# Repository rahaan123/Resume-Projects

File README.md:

# Resume-Projects
Projects listed here are mentioned on resume.

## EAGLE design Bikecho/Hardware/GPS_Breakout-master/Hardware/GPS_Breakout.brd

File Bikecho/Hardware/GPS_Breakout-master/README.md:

GPS Breakout
========================================

[  
*GPS Breakout (BOB-11818)*](https://www.sparkfun.com/products/11818)

This is a universal breakout board for any GPS units that interface over 1.0mm JST type cable. This board currently is compatible with the [GP-635T](https://www.sparkfun.com/products/11571), [GP-735](https://www.sparkfun.com/products/13670) [EM406](https://www.sparkfun.com/products/465), and [EM506](https://www.sparkfun.com/products/12751) GPS receviers and the [1 foot](https://www.sparkfun.com/products/9123) and [1.75 inch](https://www.sparkfun.com/products/574) JST cables.

Repository Contents
-------------------
* **/Hardware** - All Eagle design files (.brd, .sch)
* **/Production Files** - Test bed files and production panel files

Documentation
-------------------

* **[Hookup Guide](https://learn.sparkfun.com/tutorials/gps-basics/all#reading-gps-data)** - Basic hookup guide using the GPS breakout board.

License Information
-------------------
The hardware is released under [Creative Commons Share-alike 3.0](http://creativecommons.org/licenses/by-sa/3.0/).

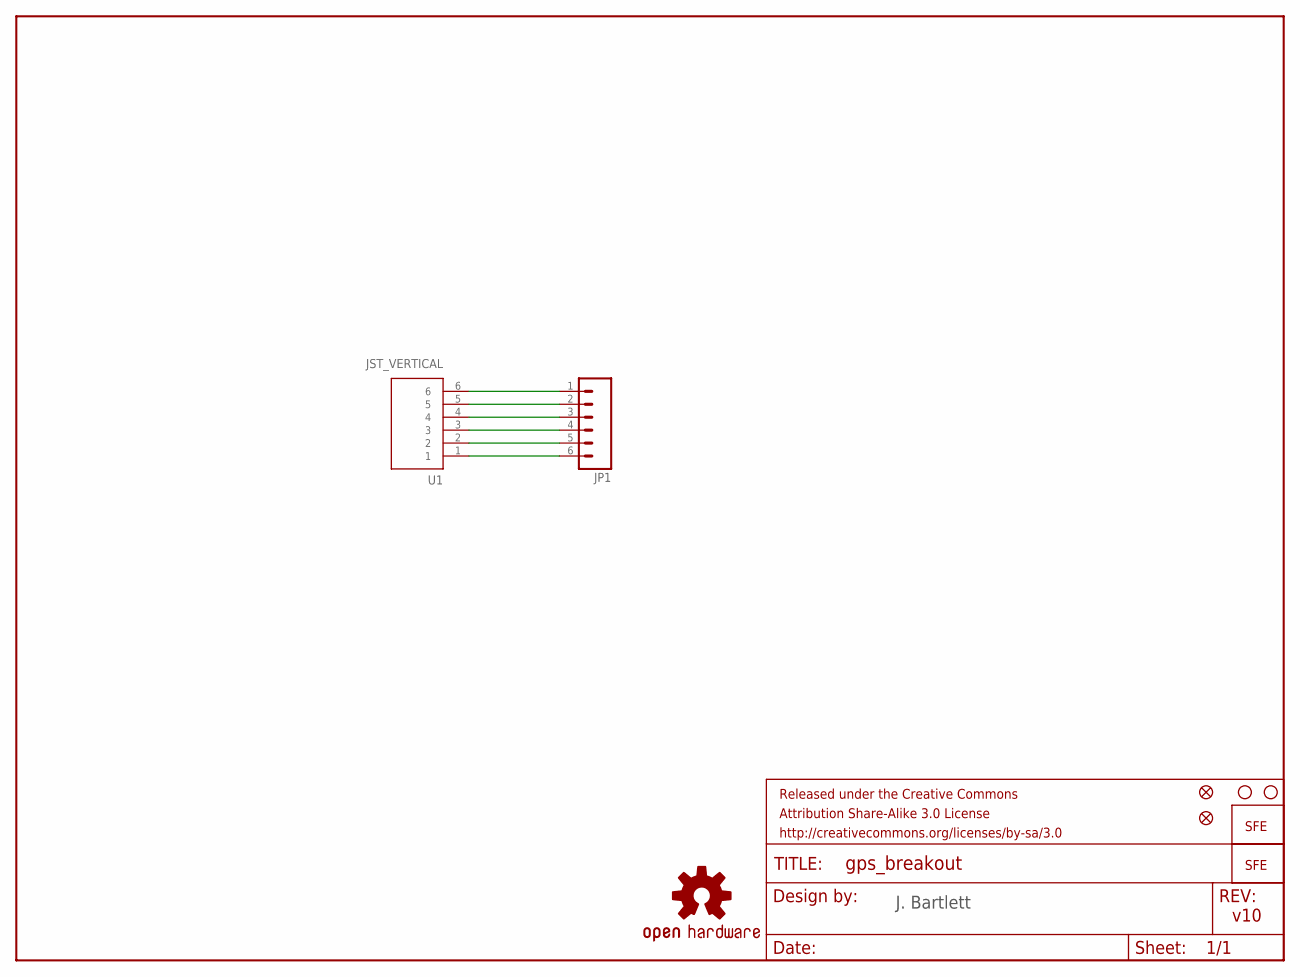
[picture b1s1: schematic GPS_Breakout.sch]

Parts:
FID1, FID2: FIDUCIALUFIDUCIAL; MICRO-FIDUCIAL
FRAME2: FRAME-LETTER; CREATIVE_COMMONS
JP1: M06SIP; 1X06
JP2, JP7: LOGO-SFESK; SFE-LOGO-FLAME
JP4, JP6: STAND-OFF
LOGO1: OSHW-LOGOS; OSHW-LOGO-S
U1: JST_VERTICAL; JST-6-SMD-VERT-1.0MM

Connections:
unnamed: JP1.1, U1.6
unnamed: JP1.2, U1.5
unnamed: JP1.3, U1.4
unnamed: JP1.4, U1.3
unnamed: JP1.5, U1.2
unnamed: JP1.6, U1.1

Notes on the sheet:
J. Bartlett
v10

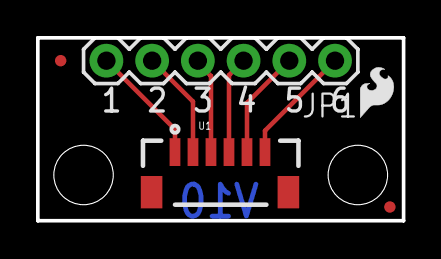
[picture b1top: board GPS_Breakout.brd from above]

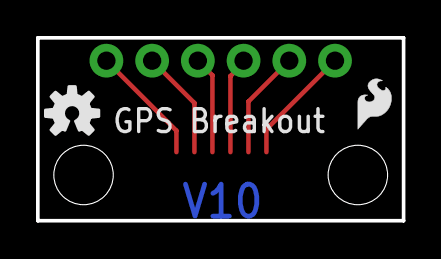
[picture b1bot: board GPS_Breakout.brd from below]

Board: 2 copper layers, 20.3 x 10.2 mm, 10 parts (2 on the bottom side), 6 nets.

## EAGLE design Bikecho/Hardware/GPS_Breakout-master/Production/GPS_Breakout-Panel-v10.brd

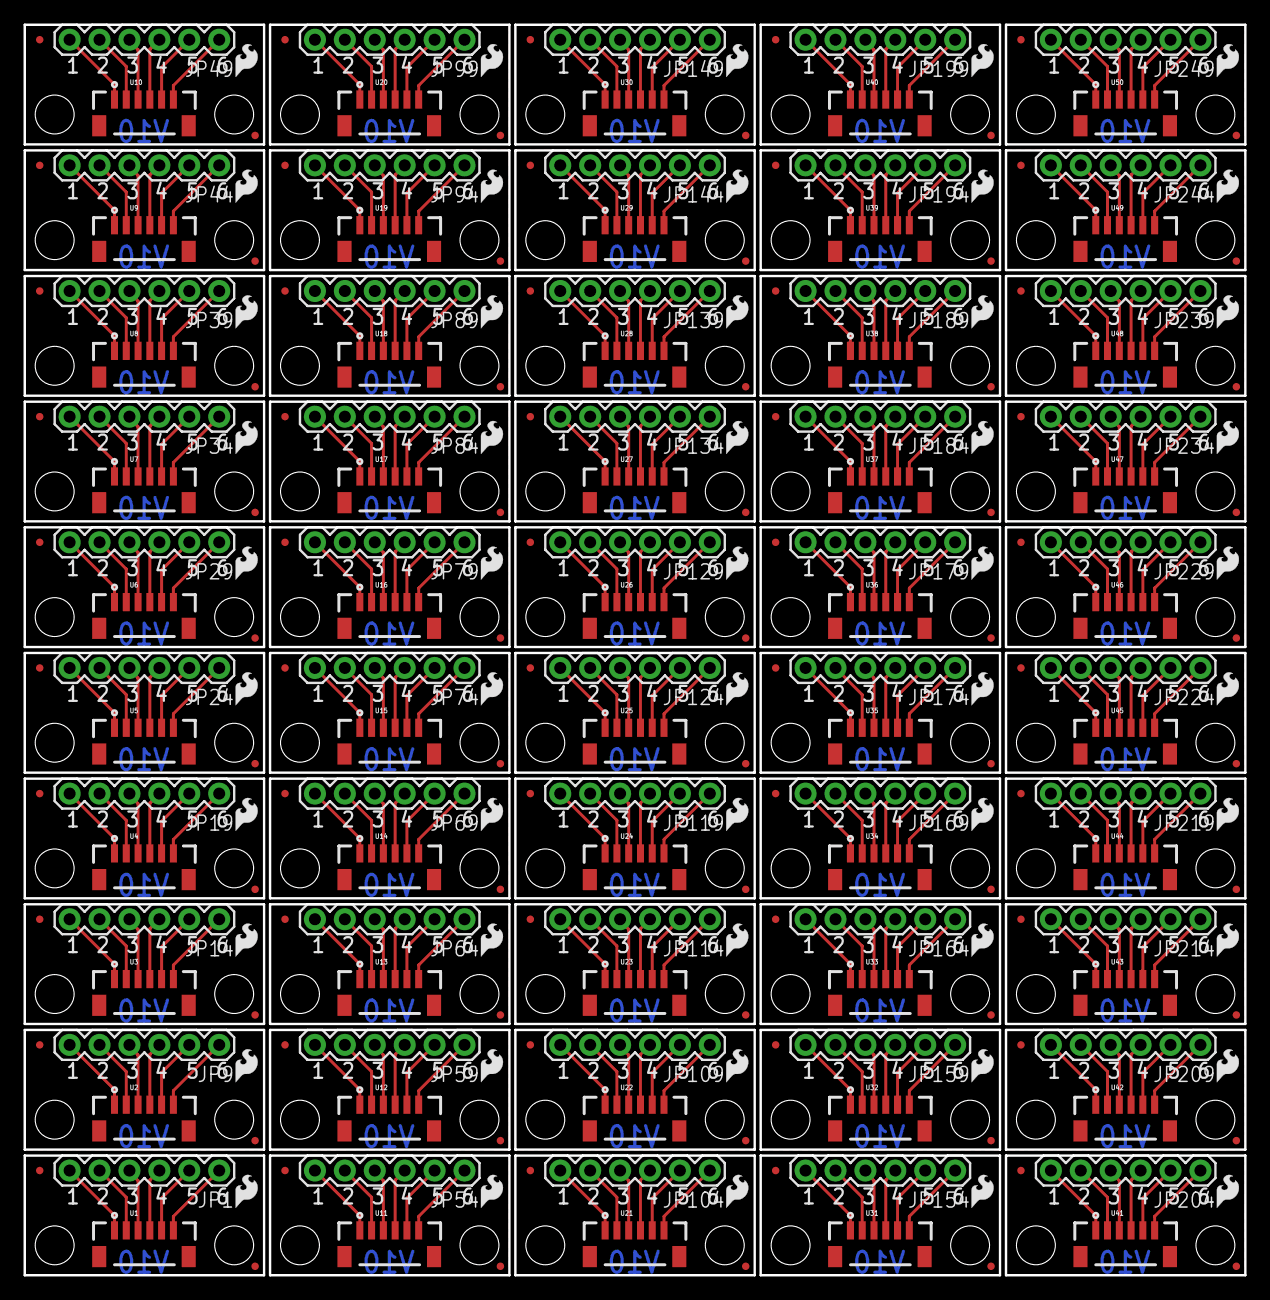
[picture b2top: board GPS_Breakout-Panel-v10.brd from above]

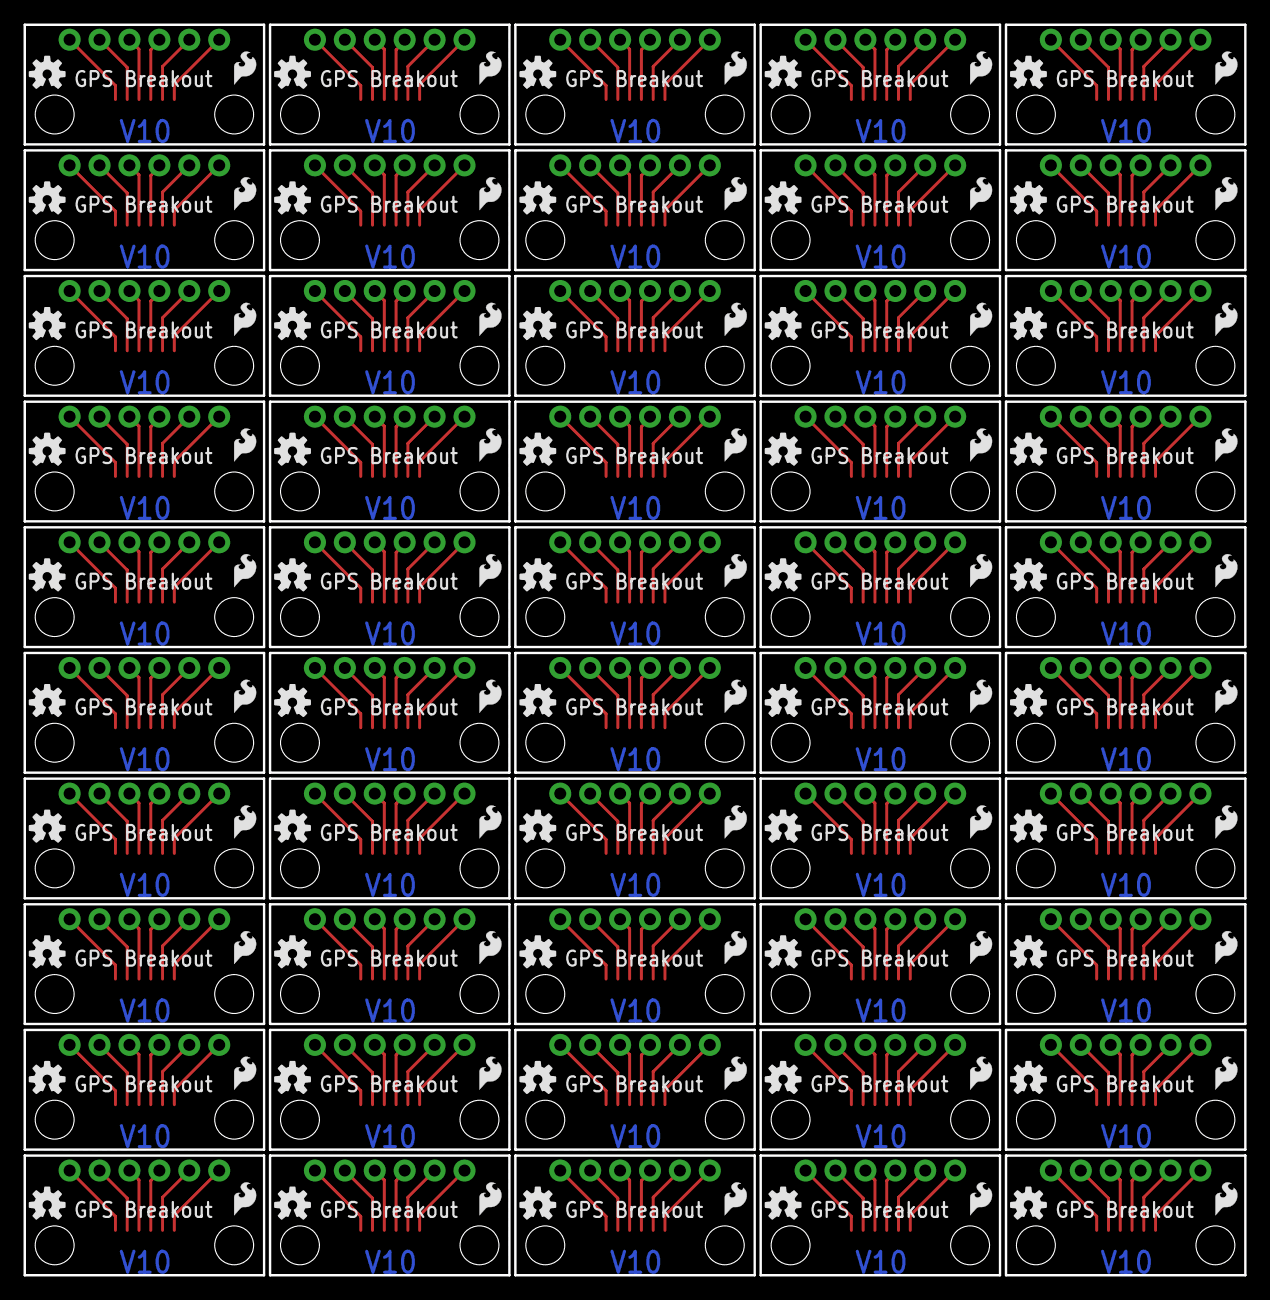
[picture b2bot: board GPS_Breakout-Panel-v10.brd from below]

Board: 2 copper layers, 103.6 x 106.2 mm, 450 parts (100 on the bottom side), 300 nets.

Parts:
FID1, FID2, FID3, FID4, FID5, FID6, FID7, FID8, FID9, FID10, FID11, FID12, FID13, FID14, FID15, FID16, FID17, FID18, FID19, FID20, FID21, FID22, FID23, FID24, FID25, FID26, FID27, FID28, FID29, FID30, FID31, FID32, FID33, FID34, FID35, FID36, FID37, FID38, FID39, FID40, FID41, FID42, FID43, FID44, FID45, FID46, FID47, FID48, FID49, FID50, FID51, FID52, FID53, FID54, FID55, FID56, FID57, FID58, FID59, FID60, FID61, FID62, FID63, FID64, FID65, FID66, FID67, FID68, FID69, FID70, FID71, FID72, FID73, FID74, FID75, FID76, FID77, FID78, FID79, FID80, FID81, FID82, FID83, FID84, FID85, FID86, FID87, FID88, FID89, FID90, FID91, FID92, FID93, FID94, FID95, FID96, FID97, FID98, FID99, FID100: FIDUCIALUFIDUCIAL; MICRO-FIDUCIAL
JP1, JP9, JP14, JP19, JP24, JP29, JP34, JP39, JP44, JP49, JP54, JP59, JP64, JP69, JP74, JP79, JP84, JP89, JP94, JP99, JP104, JP109, JP114, JP119, JP124, JP129, JP134, JP139, JP144, JP149, JP154, JP159, JP164, JP169, JP174, JP179, JP184, JP189, JP194, JP199, JP204, JP209, JP214, JP219, JP224, JP229, JP234, JP239, JP244, JP249: 1X06
JP2, JP7, JP8, JP10, JP13, JP15, JP18, JP20, JP23, JP25, JP28, JP30, JP33, JP35, JP38, JP40, JP43, JP45, JP48, JP50, JP53, JP55, JP58, JP60, JP63, JP65, JP68, JP70, JP73, JP75, JP78, JP80, JP83, JP85, JP88, JP90, JP93, JP95, JP98, JP100, JP103, JP105, JP108, JP110, JP113, JP115, JP118, JP120, JP123, JP125, JP128, JP130, JP133, JP135, JP138, JP140, JP143, JP145, JP148, JP150, JP153, JP155, JP158, JP160, JP163, JP165, JP168, JP170, JP173, JP175, JP178, JP180, JP183, JP185, JP188, JP190, JP193, JP195, JP198, JP200, JP203, JP205, JP208, JP210, JP213, JP215, JP218, JP220, JP223, JP225, JP228, JP230, JP233, JP235, JP238, JP240, JP243, JP245, JP248, JP250: LOGO-SFESK; SFE-LOGO-FLAME
JP3, JP4, JP5, JP6, JP11, JP12, JP16, JP17, JP21, JP22, JP26, JP27, JP31, JP32, JP36, JP37, JP41, JP42, JP46, JP47, JP51, JP52, JP56, JP57, JP61, JP62, JP66, JP67, JP71, JP72, JP76, JP77, JP81, JP82, JP86, JP87, JP91, JP92, JP96, JP97, JP101, JP102, JP106, JP107, JP111, JP112, JP116, JP117, JP121, JP122, JP126, JP127, JP131, JP132, JP136, JP137, JP141, JP142, JP146, JP147, JP151, JP152, JP156, JP157, JP161, JP162, JP166, JP167, JP171, JP172, JP176, JP177, JP181, JP182, JP186, JP187, JP191, JP192, JP196, JP197, JP201, JP202, JP206, JP207, JP211, JP212, JP216, JP217, JP221, JP222, JP226, JP227, JP231, JP232, JP236, JP237, JP241, JP242, JP246, JP247: STAND-OFF
LOGO1, LOGO2, LOGO3, LOGO4, LOGO5, LOGO6, LOGO7, LOGO8, LOGO9, LOGO10, LOGO11, LOGO12, LOGO13, LOGO14, LOGO15, LOGO16, LOGO17, LOGO18, LOGO19, LOGO20, LOGO21, LOGO22, LOGO23, LOGO24, LOGO25, LOGO26, LOGO27, LOGO28, LOGO29, LOGO30, LOGO31, LOGO32, LOGO33, LOGO34, LOGO35, LOGO36, LOGO37, LOGO38, LOGO39, LOGO40, LOGO41, LOGO42, LOGO43, LOGO44, LOGO45, LOGO46, LOGO47, LOGO48, LOGO49, LOGO50: OSHW-LOGOS; OSHW-LOGO-S
U1, U2, U3, U4, U5, U6, U7, U8, U9, U10, U11, U12, U13, U14, U15, U16, U17, U18, U19, U20, U21, U22, U23, U24, U25, U26, U27, U28, U29, U30, U31, U32, U33, U34, U35, U36, U37, U38, U39, U40, U41, U42, U43, U44, U45, U46, U47, U48, U49, U50: JST_VERTICAL; JST-6-SMD-VERT-1.0MM

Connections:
unnamed: JP1.1, U1.6
unnamed: JP1.2, U1.5
unnamed: JP1.3, U1.4
unnamed: JP1.4, U1.3
unnamed: JP1.5, U1.2
unnamed: JP1.6, U1.1
unnamed: JP9.1, U2.6
unnamed: JP9.2, U2.5
unnamed: JP9.3, U2.4
unnamed: JP9.4, U2.3
unnamed: JP9.5, U2.2
unnamed: JP9.6, U2.1
unnamed: JP14.1, U3.6
unnamed: JP14.2, U3.5
unnamed: JP14.3, U3.4
unnamed: JP14.4, U3.3
unnamed: JP14.5, U3.2
unnamed: JP14.6, U3.1
unnamed: JP19.1, U4.6
unnamed: JP19.2, U4.5
unnamed: JP19.3, U4.4
unnamed: JP19.4, U4.3
unnamed: JP19.5, U4.2
unnamed: JP19.6, U4.1
unnamed: JP24.1, U5.6
unnamed: JP24.2, U5.5
unnamed: JP24.3, U5.4
unnamed: JP24.4, U5.3
unnamed: JP24.5, U5.2
unnamed: JP24.6, U5.1
unnamed: JP29.1, U6.6
unnamed: JP29.2, U6.5
unnamed: JP29.3, U6.4
unnamed: JP29.4, U6.3
unnamed: JP29.5, U6.2
unnamed: JP29.6, U6.1
unnamed: JP34.1, U7.6
unnamed: JP34.2, U7.5
unnamed: JP34.3, U7.4
unnamed: JP34.4, U7.3
unnamed: JP34.5, U7.2
unnamed: JP34.6, U7.1
unnamed: JP39.1, U8.6
unnamed: JP39.2, U8.5
unnamed: JP39.3, U8.4
unnamed: JP39.4, U8.3
unnamed: JP39.5, U8.2
unnamed: JP39.6, U8.1
unnamed: JP44.1, U9.6
unnamed: JP44.2, U9.5
unnamed: JP44.3, U9.4
unnamed: JP44.4, U9.3
unnamed: JP44.5, U9.2
unnamed: JP44.6, U9.1
unnamed: JP49.1, U10.6
unnamed: JP49.2, U10.5
unnamed: JP49.3, U10.4
unnamed: JP49.4, U10.3
unnamed: JP49.5, U10.2
unnamed: JP49.6, U10.1
unnamed: JP54.1, U11.6
unnamed: JP54.2, U11.5
unnamed: JP54.3, U11.4
unnamed: JP54.4, U11.3
unnamed: JP54.5, U11.2
unnamed: JP54.6, U11.1
unnamed: JP59.1, U12.6
unnamed: JP59.2, U12.5
unnamed: JP59.3, U12.4
unnamed: JP59.4, U12.3
unnamed: JP59.5, U12.2
unnamed: JP59.6, U12.1
unnamed: JP64.1, U13.6
unnamed: JP64.2, U13.5
unnamed: JP64.3, U13.4
unnamed: JP64.4, U13.3
unnamed: JP64.5, U13.2
unnamed: JP64.6, U13.1
unnamed: JP69.1, U14.6
unnamed: JP69.2, U14.5
unnamed: JP69.3, U14.4
unnamed: JP69.4, U14.3
unnamed: JP69.5, U14.2
unnamed: JP69.6, U14.1
unnamed: JP74.1, U15.6
unnamed: JP74.2, U15.5
unnamed: JP74.3, U15.4
unnamed: JP74.4, U15.3
unnamed: JP74.5, U15.2
unnamed: JP74.6, U15.1
unnamed: JP79.1, U16.6
unnamed: JP79.2, U16.5
unnamed: JP79.3, U16.4
unnamed: JP79.4, U16.3
unnamed: JP79.5, U16.2
unnamed: JP79.6, U16.1
unnamed: JP84.1, U17.6
unnamed: JP84.2, U17.5
unnamed: JP84.3, U17.4
unnamed: JP84.4, U17.3
unnamed: JP84.5, U17.2
unnamed: JP84.6, U17.1
unnamed: JP89.1, U18.6
unnamed: JP89.2, U18.5
unnamed: JP89.3, U18.4
unnamed: JP89.4, U18.3
unnamed: JP89.5, U18.2
unnamed: JP89.6, U18.1
unnamed: JP94.1, U19.6
unnamed: JP94.2, U19.5
unnamed: JP94.3, U19.4
unnamed: JP94.4, U19.3
unnamed: JP94.5, U19.2
unnamed: JP94.6, U19.1
unnamed: JP99.1, U20.6
unnamed: JP99.2, U20.5
unnamed: JP99.3, U20.4
unnamed: JP99.4, U20.3
unnamed: JP99.5, U20.2
unnamed: JP99.6, U20.1
unnamed: JP104.1, U21.6
unnamed: JP104.2, U21.5
unnamed: JP104.3, U21.4
unnamed: JP104.4, U21.3
unnamed: JP104.5, U21.2
unnamed: JP104.6, U21.1
unnamed: JP109.1, U22.6
unnamed: JP109.2, U22.5
unnamed: JP109.3, U22.4
unnamed: JP109.4, U22.3
unnamed: JP109.5, U22.2
unnamed: JP109.6, U22.1
unnamed: JP114.1, U23.6
unnamed: JP114.2, U23.5
unnamed: JP114.3, U23.4
unnamed: JP114.4, U23.3
unnamed: JP114.5, U23.2
unnamed: JP114.6, U23.1
unnamed: JP119.1, U24.6
unnamed: JP119.2, U24.5
unnamed: JP119.3, U24.4
unnamed: JP119.4, U24.3
unnamed: JP119.5, U24.2
unnamed: JP119.6, U24.1
unnamed: JP124.1, U25.6
unnamed: JP124.2, U25.5
unnamed: JP124.3, U25.4
unnamed: JP124.4, U25.3
unnamed: JP124.5, U25.2
unnamed: JP124.6, U25.1
unnamed: JP129.1, U26.6
unnamed: JP129.2, U26.5
unnamed: JP129.3, U26.4
unnamed: JP129.4, U26.3
unnamed: JP129.5, U26.2
unnamed: JP129.6, U26.1
unnamed: JP134.1, U27.6
unnamed: JP134.2, U27.5
unnamed: JP134.3, U27.4
unnamed: JP134.4, U27.3
unnamed: JP134.5, U27.2
unnamed: JP134.6, U27.1
unnamed: JP139.1, U28.6
unnamed: JP139.2, U28.5
unnamed: JP139.3, U28.4
unnamed: JP139.4, U28.3
unnamed: JP139.5, U28.2
unnamed: JP139.6, U28.1
unnamed: JP144.1, U29.6
unnamed: JP144.2, U29.5
unnamed: JP144.3, U29.4
unnamed: JP144.4, U29.3
unnamed: JP144.5, U29.2
unnamed: JP144.6, U29.1
unnamed: JP149.1, U30.6
unnamed: JP149.2, U30.5
unnamed: JP149.3, U30.4
unnamed: JP149.4, U30.3
unnamed: JP149.5, U30.2
unnamed: JP149.6, U30.1
unnamed: JP154.1, U31.6
unnamed: JP154.2, U31.5
unnamed: JP154.3, U31.4
unnamed: JP154.4, U31.3
unnamed: JP154.5, U31.2
unnamed: JP154.6, U31.1
unnamed: JP159.1, U32.6
unnamed: JP159.2, U32.5
unnamed: JP159.3, U32.4
unnamed: JP159.4, U32.3
unnamed: JP159.5, U32.2
unnamed: JP159.6, U32.1
unnamed: JP164.1, U33.6
unnamed: JP164.2, U33.5
unnamed: JP164.3, U33.4
unnamed: JP164.4, U33.3
unnamed: JP164.5, U33.2
unnamed: JP164.6, U33.1
unnamed: JP169.1, U34.6
unnamed: JP169.2, U34.5
unnamed: JP169.3, U34.4
unnamed: JP169.4, U34.3
unnamed: JP169.5, U34.2
unnamed: JP169.6, U34.1
unnamed: JP174.1, U35.6
unnamed: JP174.2, U35.5
unnamed: JP174.3, U35.4
unnamed: JP174.4, U35.3
unnamed: JP174.5, U35.2
unnamed: JP174.6, U35.1
unnamed: JP179.1, U36.6
unnamed: JP179.2, U36.5
unnamed: JP179.3, U36.4
unnamed: JP179.4, U36.3
unnamed: JP179.5, U36.2
unnamed: JP179.6, U36.1
unnamed: JP184.1, U37.6
unnamed: JP184.2, U37.5
unnamed: JP184.3, U37.4
unnamed: JP184.4, U37.3
unnamed: JP184.5, U37.2
unnamed: JP184.6, U37.1
unnamed: JP189.1, U38.6
unnamed: JP189.2, U38.5
unnamed: JP189.3, U38.4
unnamed: JP189.4, U38.3
unnamed: JP189.5, U38.2
unnamed: JP189.6, U38.1
unnamed: JP194.1, U39.6
unnamed: JP194.2, U39.5
unnamed: JP194.3, U39.4
unnamed: JP194.4, U39.3
unnamed: JP194.5, U39.2
unnamed: JP194.6, U39.1
unnamed: JP199.1, U40.6
unnamed: JP199.2, U40.5
unnamed: JP199.3, U40.4
unnamed: JP199.4, U40.3
unnamed: JP199.5, U40.2
unnamed: JP199.6, U40.1
unnamed: JP204.1, U41.6
unnamed: JP204.2, U41.5
unnamed: JP204.3, U41.4
unnamed: JP204.4, U41.3
unnamed: JP204.5, U41.2
unnamed: JP204.6, U41.1
unnamed: JP209.1, U42.6
unnamed: JP209.2, U42.5
unnamed: JP209.3, U42.4
unnamed: JP209.4, U42.3
unnamed: JP209.5, U42.2
unnamed: JP209.6, U42.1
unnamed: JP214.1, U43.6
unnamed: JP214.2, U43.5
unnamed: JP214.3, U43.4
unnamed: JP214.4, U43.3
unnamed: JP214.5, U43.2
unnamed: JP214.6, U43.1
unnamed: JP219.1, U44.6
unnamed: JP219.2, U44.5
unnamed: JP219.3, U44.4
unnamed: JP219.4, U44.3
unnamed: JP219.5, U44.2
unnamed: JP219.6, U44.1
unnamed: JP224.1, U45.6
unnamed: JP224.2, U45.5
unnamed: JP224.3, U45.4
unnamed: JP224.4, U45.3
unnamed: JP224.5, U45.2
unnamed: JP224.6, U45.1
unnamed: JP229.1, U46.6
unnamed: JP229.2, U46.5
unnamed: JP229.3, U46.4
unnamed: JP229.4, U46.3
unnamed: JP229.5, U46.2
unnamed: JP229.6, U46.1
unnamed: JP234.1, U47.6
unnamed: JP234.2, U47.5
unnamed: JP234.3, U47.4
unnamed: JP234.4, U47.3
unnamed: JP234.5, U47.2
unnamed: JP234.6, U47.1
unnamed: JP239.1, U48.6
unnamed: JP239.2, U48.5
unnamed: JP239.3, U48.4
unnamed: JP239.4, U48.3
unnamed: JP239.5, U48.2
unnamed: JP239.6, U48.1
unnamed: JP244.1, U49.6
unnamed: JP244.2, U49.5
unnamed: JP244.3, U49.4
unnamed: JP244.4, U49.3
unnamed: JP244.5, U49.2
unnamed: JP244.6, U49.1
unnamed: JP249.1, U50.6
unnamed: JP249.2, U50.5
unnamed: JP249.3, U50.4
unnamed: JP249.4, U50.3
unnamed: JP249.5, U50.2
unnamed: JP249.6, U50.1

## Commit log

2021-06-02 Pet classifier project
2021-06-02 create
2021-06-02 Fitness VR project
2023-12-24 Rename CSCE_633_Final_Project_code_Rahaan_Gandhi.ipynb to Yelp Restuarant reviews classifier
2023-12-24 Create read
2023-12-24 Rename Yelp Restuarant reviews classifier to yelp reviews/Yelp Restuarant reviews classifier
2023-12-24 Create empty
2024-03-31 Create temp
2024-03-31 Rename temp to temp
2024-03-31 adding dataset.csv
2024-04-04 Rename Yelp Restuarant reviews classifier to Yelp Restuarant reviews classifier
2025-03-19 Create init
2025-03-19 Rename CSCE 689 HW2 Rahaan Gandhi.zip to Analyzing bias lvl2
2025-03-19 Rename CSCE_689_hw1_Rahaan_Gandhi.zip to analyzing bias lvl1
2025-03-28 Rename readme to readme
2025-03-28 rename
2025-05-18 Rename recog.cpp to recog.py
2025-05-18 Rename requirements.txt to Smart Home Automation System/requirements.txt
2025-08-03 Java proj 1

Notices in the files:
parts and their libraries:
SparkFun-Connectors: Licensing: CC v3.0 Share-Alike You are welcome to use this library for commercial purposes.
SparkFun-Aesthetics: Released under the Creative Commons Attribution Share-Alike 3.0 License
SparkFun-Aesthetics: Released under the Creative Commons
